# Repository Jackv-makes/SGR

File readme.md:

# SGR(Simple Gameboy Regulator)
This is a very basic Gameboy Pocket/Color regulator made in KiCad. It supplies 5V and can be used with the modern display kits, but it will not work with the oem display. The reason for the creation of this regulator is to offer an open source Gameboy Pocket/Color regulator that is easy to build.

# Features
- Supplies 5V voltage to Gameboy Pocket/Color
- Easy to build, only needing 6 components
- Removes the need for C32 on the Gameboy Color(I would advise that it is left in place, unless it is broken)
- Can be manufactured in any color you like to match your theme
- Open Sourced, so you can do anything you want with it(fun shapes, artwork, etc.)

# Disclaimer
Even though is board was made to be extremely easy, it still does require some basic soldering skill to build and a basic understanding of electronics to test. I am by no means a professional electronics engineer and only do this as a hobby, if you see any improvements that you would like to make; feel free to fork the repo. Please note that this regulator WILL NOT work with the oem display because it does not include the needed voltage lines for it.

Troubleshooting is done at my discretion, the design is simple enough that it will either work or not. I am not responsible for blown fuses, fires, injuries, etc. that may happen if things are done incorrectly.

# Ordering
The board can be ordered at any PCB manufacturer of your choice, if you choose to use PCBWay through my shared project link, I get a small commission. These can be ordered in any thickness and finish. I recommend around 1.2mm thickness and HASL. I've included two gerber files, one with the components on the back of the board(reverse) and one with the components on the front.

[PCBWay Project](https://www.pcbway.com/project/shareproject/SGR_Simple_Gameboy_Regulator_e071975c.html)

# Bill of Materials & Assembly
The board has only 6 components, which are all surface mounted and do require some basic soldering skills to build. If you are not very experienced, you will probably have a harder time with desoldering the existing regulator than soldering this one on. If you don't trust yourself with building one, you can order them assembled from PCBWay/JLC. Don't forget to buy some 2.54mm header pins!

# Credit and Thanks

Credit to marshallh for the board outline and people in the Gameboy Community for their continued support!

- [marshallh's github](https://github.com/marshallh/gbpp/tree/main)
- [Gameboy Discord](https://discord.gg/xywcXQVD)
- [Modded Gameboy Club](https://discord.gg/79MY8BsW)

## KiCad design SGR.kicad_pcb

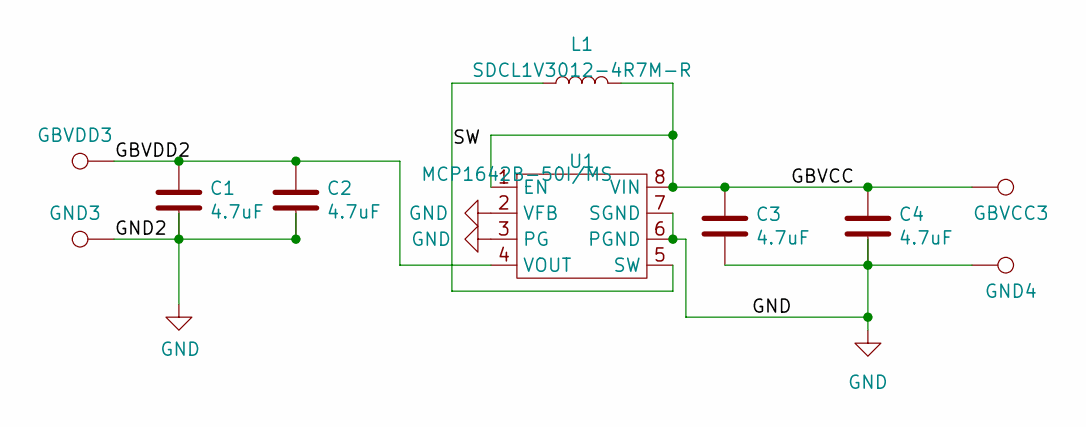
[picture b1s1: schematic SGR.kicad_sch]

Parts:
C1, C2, C3, C4: 4.7uF; C_0805_2012Metric; Mouser 81-GRM21BR71C475KE1L
GBVCC3: Hole
GBVDD3: Hole
GND3, GND4: Hole
L1: SDCL1V3012-4R7M-R; INDUCTOR3x3
U1: MCP1642B-50I/MS; MSOP-8_3x3mm_P0.65mm

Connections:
/GBVCC: C3.1, C4.1, GBVCC3.1, L1.2, U1.1 (EN), U1.8 (VIN)
/GBVDD2: C1.1, C2.1, GBVDD3.1, U1.4 (VOUT)
/SW: L1.1, U1.5 (SW)
GND: C1.2, C2.2, C3.2, C4.2, GND3.1, GND4.1, U1.2 (VFB), U1.3 (PG), U1.6 (PGND), U1.7 (SGND)

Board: 2 copper layers, 10 parts (0 on the bottom side), 4 nets, no tracks yet.

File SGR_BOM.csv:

Designator,Footprint,Quantity,Value,Digikey Urls
"C1, C2, C3, C4",805,4,4.7uF,https://www.digikey.com/en/products/detail/samsung-electro-m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
L1,IND_3x3_SMD,1,SDCL1V3012-4R7M-R,https://www.digikey.com/en/products/detail/eaton-electronics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
L1(Alternative),1008,1,LQM2HPN4R7MG0L,https://www.digikey.com/en/products/detail/eaton-electronics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
U1,8-MSOP,1,MCP1642B-50I/MS,https://www.digikey.com/en/products/detail/murata-electronic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

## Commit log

2024-09-13 Rename SGR_V1.1.zip to SGR_V1.1_GERBERS.zip
2024-09-13 Rename REVERSE_SGR_V1.1_GERBERS.zip to SGR_REVERSE_V1.1_GERBERS.zip
2024-09-28 Rename cc-by-4.0.txt to LICENSE.md
